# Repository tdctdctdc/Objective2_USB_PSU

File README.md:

# Objective2_USB_PSU
Isolated USB power supply for the Objective 2 Headphone Amp

Board fit in the battery compartment
held in place using Hole1 (M3)

Basic circuit with isolated traco module and some luxury LDO.
3 footprint for TEM, TBA and TEC dual output voltage converter (5V to +/- 15V or 12 V)

R1,R2,R3,R4 can be optmized to fit more common E series i think

it works

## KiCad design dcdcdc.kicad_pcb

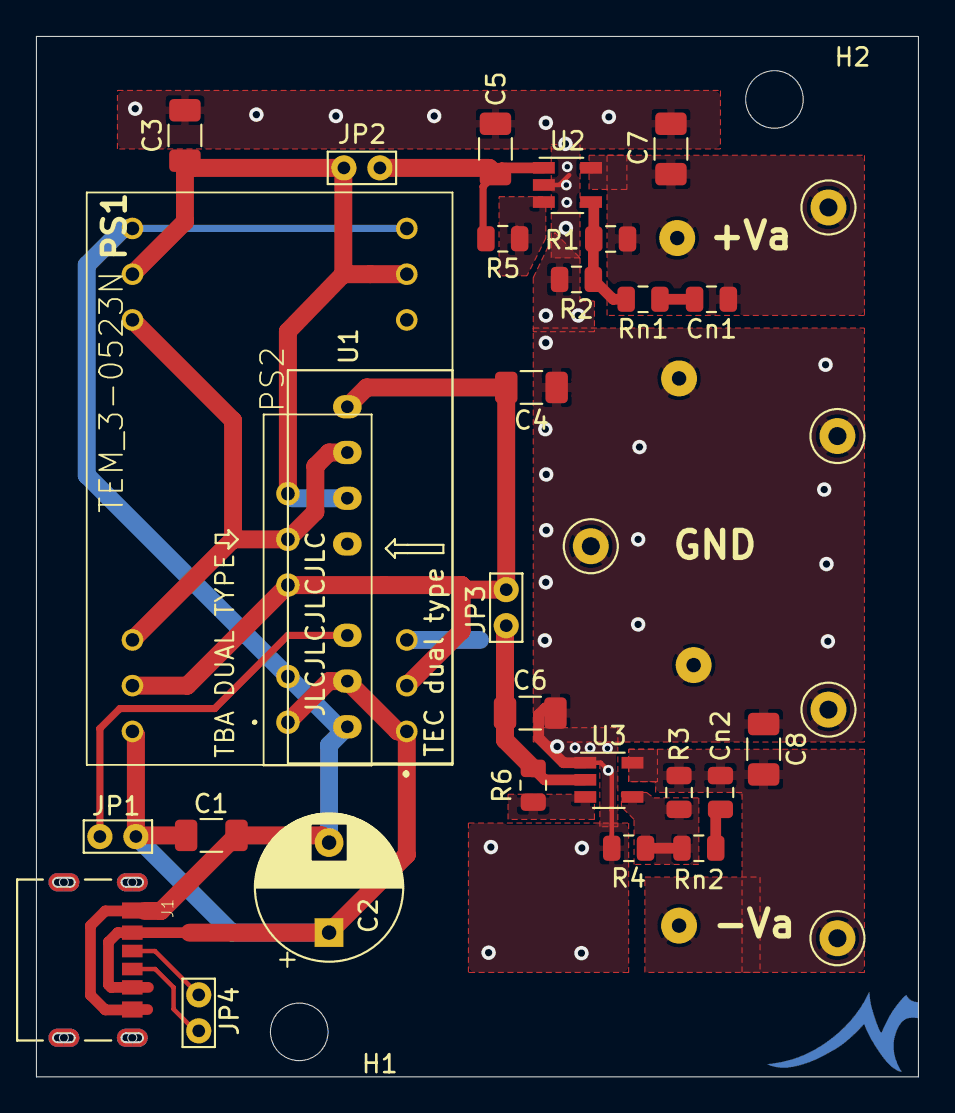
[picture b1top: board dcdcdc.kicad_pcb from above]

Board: 2 copper layers, 49.0 x 57.8 mm, 39 parts (0 on the bottom side), 19 nets.

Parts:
C1: CP_Small; C_1206_3216Metric
C2: CP_Small; CP_Radial_D8.0mm_P5.00mm
C3, C4: 220u; C_1206_3216Metric
C5, C6, C7, C8: 4.7u; C_1206_3216Metric
Cn1: 1u; C_0805_2012Metric
Cn2: 100n; C_0805_2012Metric
H1, H2: MountingHole; MountingHole_3.2mm_M3
J1: UJC-HP-3-SMT-TR; CUI_UJC-HP-3-SMT-TR
J2, J3, J3#2, J3#3, J4: Screw_Terminal_01x01; TestPoint_Loop_D1.80mm_Drill1.0mm_Beaded
JP1, JP2, JP3, JP4: Jumper_NC_Small; TestPoint_Bridge_Pitch2.0mm_Drill0.7mm
PS1: TEM_3-0523N; TEM30523N
PS2: TBA DUAL TYPE; TBA10522E
R1: 240k; R_0805_2012Metric
R2: 22.1k; R_0805_2012Metric
R3: 218k; R_0805_2012Metric
R4: 20.5k; R_0805_2012Metric
R5, R6: 0R; R_0805_2012Metric
Rn1: 1k; R_0805_2012Metric
Rn2: 13k; R_0805_2012Metric
TP1, TP2, TP3, TP4: TestPoint; SolderWirePad_1x01_Drill0.8mm
U1: TEC_2-0923; TEC_2-0523
U2: ADP7142AUJZ; TSOT-23-5
U3: ADP7182AUJZ; TSOT-23-5

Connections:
/+Va: C7.1, Cn1.1, J2.1, R1.1, TP2.1, U2.5
/+Vo: C3.1, JP2.1, PS1.11, PS1.14, PS2.6, U1.6
/-Va: C8.2, Cn2.2, J4.1, R3.2, TP3.1, U3.5
/-Vo: C4.2, JP3.1, PS1.2, PS1.23, PS2.4, U1.8
/GNDusb: C1.2, C2.2, J1.A12, J1.B12, PS1.12, PS1.13, PS2.2, U1.1
/Vusb: C1.1, C2.1, J1.A9, J1.B9, JP1.1, PS1.1, PS1.24, PS2.1, U1.2
GNDA: C3.2, C4.1, C5.1, C6.2, C7.2, C8.1, J3.1, J3#2.1, J3#3.1, PS1.3, PS1.10, PS1.15, PS1.22, PS2.5, R2.2, R4.1, TP1.1, TP4.1, U1.7, U2.2, U3.1
unnamed: C5.2, JP2.2, R5.2, U2.1
unnamed: C6.1, JP3.2, R6.1, U3.2
unnamed: Cn1.2, Rn1.1
unnamed: Cn2.1, Rn2.1
unnamed: J1.A5, JP4.2
unnamed: J1.B5, JP4.1
unnamed: J1.S1, J1.S2, J1.S3, J1.S4
unnamed: JP1.2, U1.3
unnamed: R1.2, R2.1, Rn1.2, U2.4
unnamed: R3.1, R4.2, Rn2.2, U3.4
unnamed: R5.1, U2.3
unnamed: R6.2, U3.3

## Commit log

2021-08-22 terrible solder job
